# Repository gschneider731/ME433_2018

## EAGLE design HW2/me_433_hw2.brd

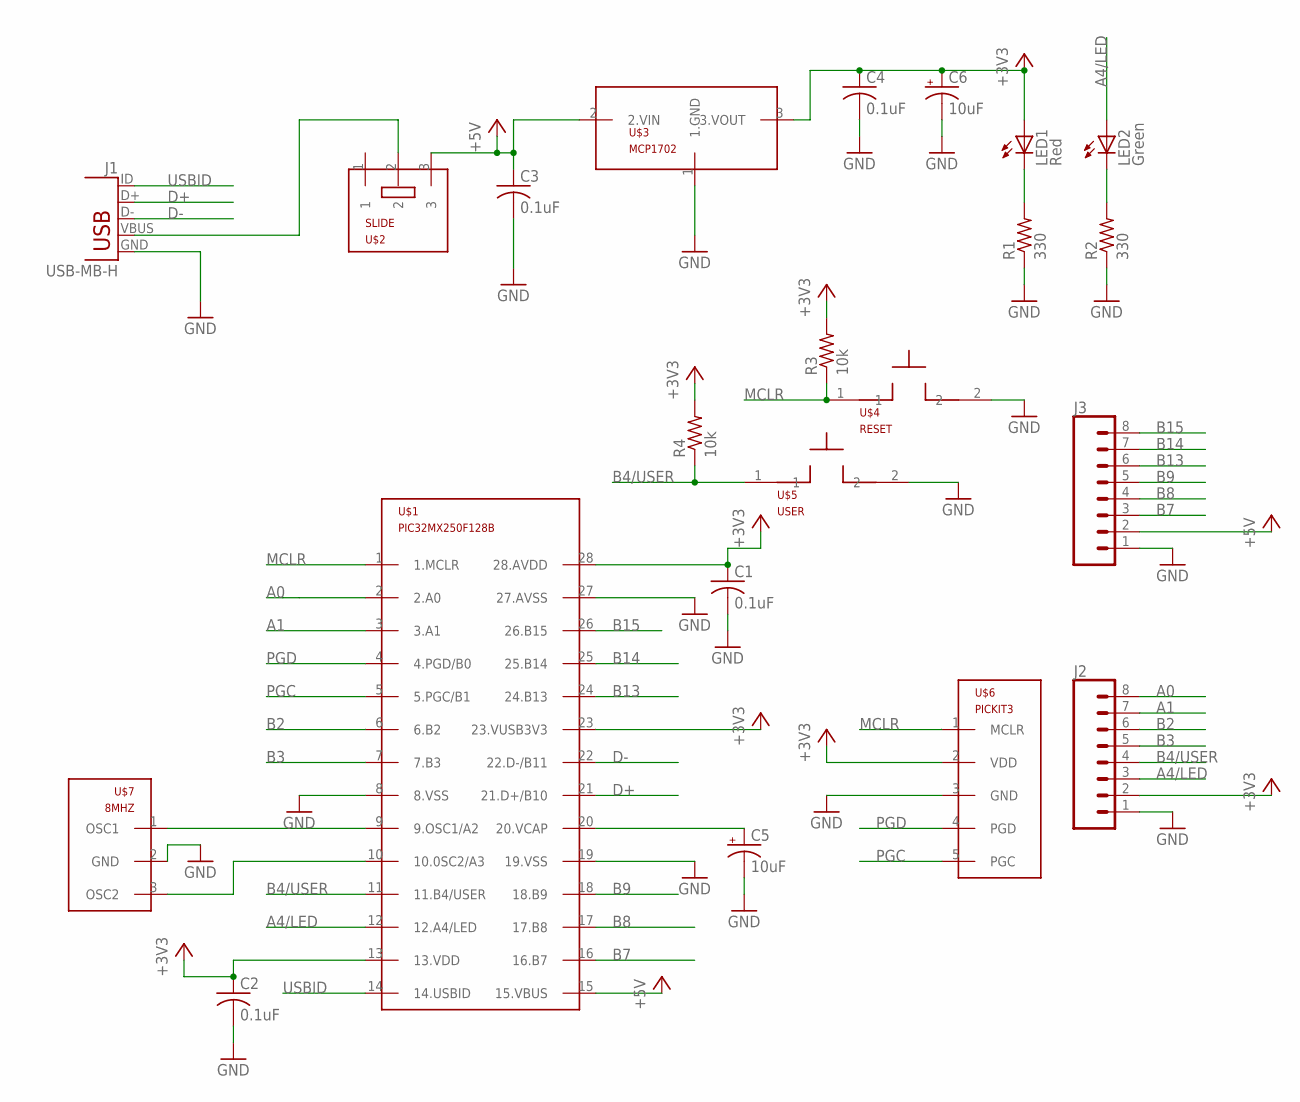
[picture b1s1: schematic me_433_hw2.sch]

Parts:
C1, C2, C3, C4: 0.1uF; C025-025X050
C5, C6: 10uF; B45181B
J1: USB-MB-H
J2, J3: CONN_08; 1X08
LED1: Red; LED3MM
LED2: Green; LED3MM
R1, R2: 330; 0207/10
R3, R4: 10k; 0207/10
U$1: PIC32MX250F128B; DIL28-3
U$2: SLIDE
U$3: MCP1702; TO92
U$4: RESET; PB
U$5: USER; PB
U$6: PICKIT3; 1X05
U$7: 8MHZ; OSC

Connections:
+3V3: C1.1, C2.1, C4.1, C6.+, J2.2, LED1.A, R3.2, R4.2, U$1.13 (13.VDD), U$1.23 (23.VUSB3V3), U$1.28 (28.AVDD), U$3.3 (3.VOUT), U$6.2 (VDD)
+5V: C3.1, J3.2, U$1.15 (15.VBUS), U$2.3, U$3.2 (2.VIN)
A0: J2.8, U$1.2 (2.A0)
A1: J2.7, U$1.3 (3.A1)
A4/LED: J2.3, LED2.A, U$1.12 (12.A4/LED)
B2: J2.6, U$1.6 (6.B2)
B3: J2.5, U$1.7 (7.B3)
B4/USER: J2.4, R4.1, U$1.11 (11.B4/USER), U$5.1
B7: J3.3, U$1.16 (16.B7)
B8: J3.4, U$1.17 (17.B8)
B9: J3.5, U$1.18 (18.B9)
B13: J3.6, U$1.24 (24.B13)
B14: J3.7, U$1.25 (25.B14)
B15: J3.8, U$1.26 (26.B15)
D+: J1.D+, U$1.21 (21.D+/B10)
D-: J1.D-, U$1.22 (22.D-/B11)
GND: C1.2, C2.2, C3.2, C4.2, C5.-, C6.-, J1.GND, J2.1, J3.1, R1.1, R2.1, U$1.8 (8.VSS), U$1.19 (19.VSS), U$1.27 (27.AVSS), U$3.1 (1.GND), U$4.2, U$5.2, U$6.3 (GND), U$7.2 (GND)
MCLR: R3.1, U$1.1 (1.MCLR), U$4.1, U$6.1 (MCLR)
unnamed: J1.VBUS, U$2.2
unnamed: U$1.9 (9.OSC1/A2), U$7.1 (OSC1)
unnamed: U$1.10 (10.0SC2/A3), U$7.3 (OSC2)
unnamed: LED1.K (C), R1.2
unnamed: C5.+, U$1.20 (20.VCAP)
unnamed: LED2.K (C), R2.2
PGC: U$1.5 (5.PGC/B1), U$6.5 (PGC)
PGD: U$1.4 (4.PGD/B0), U$6.4 (PGD)
USBID: J1.ID, U$1.14 (14.USBID)

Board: 2 copper layers, 22 parts (0 on the bottom side), 27 nets, no tracks yet.

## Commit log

2018-04-08 Verified Green LED turns on
2018-04-09 Final code demonstrating 1kHz square wave with button push
2018-04-09 Actual final code demonstrating 1kHz square wave with button push
2018-04-12 Create HW2
2018-04-18 Had 1.7 constant V, added parts for sine and triangle waves
2018-04-19 Updated Code, needs to be tested with an oscilloscope
2018-04-19 Waveform Output - Incorrect
2018-04-22 Adjustments to HW 4 and 5
2018-04-24 Code for HW5 - untested (circuit is broken - cannot do HW1)
2018-04-24 minor edits/testing performed while testing HW5
2018-04-24 HW6 Setup
2018-04-25 Added drawChar and drawString functions
2018-04-25 HW6 Final Code
2018-05-01 HW7 edits
2018-05-01 Added code for the progress bar
2018-05-01 Minor edits to HW7
2018-05-01 Final Code HW7
2018-05-01 HW8 with HW1 code working
2018-05-01 HW8_Final with code from HW7 working
2018-05-08 Final HW9 code
2018-05-08 New Final HW9 code
2018-05-13 Created HW10 files
2018-05-13 Various Updates
2018-05-13 Switched everything from HW10 to HW10_1 to get a working project
2018-05-14 HW10_1 breaks from reading values when z acceleration gets too high
2018-05-14 Final Code w/ plot, explanation, and MATLAB file
2018-05-15 Final HW5
2018-05-15 Built HW11
2018-05-15 HW11 edits
2018-05-16 Hello World working
2018-05-17 HW12 working
2018-05-20 HW13 working with slider bar
2018-05-20 Adjusted code to stop labeling blue as green
2018-05-24 Created HW14 codes
2018-05-24 USB doesn't seem to work
2018-05-24 testing
2018-05-24 HW14 working
2018-06-07 HW11 completed
2018-06-07 CAD Designs and 3D Printed Wheel
2018-06-11 HW15 Box Pic
2018-06-11 Minor Edits
2018-06-11 HW16 Created
2018-06-11 HW17 Working
2018-06-11 HW17 Final
2018-06-11 Added HW17 Video
2018-06-12 HW16 pic code modified and android code added
2018-06-12 HW16 Final
2018-06-12 Added HW16 Video
2018-06-12 HW18 Created
2018-06-12 HW18 Updates
2018-06-12 Sends motor power based on position
2018-06-12 Not following curves yet
2018-06-13 In theory, this code would collect four data points along the line and turn based on the middle two...but I cannot test it as my phone is no longer recognized by the usb
2018-06-13 Phone is now working with USB, but is also now dead. Code should work somewhat for line following
2018-06-13 Final Code
